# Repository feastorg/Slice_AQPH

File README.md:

# Slice Template

Template for creating BREAD slices.

## Introduction

[Short introduction on the project.]

## Usage

[Explain how to use the project. Include examples and screenshots if applicable.]

## pH front end

The pH electrode connects to the BNC (J2). U2 (CA3140) amplifies its EMF and
U4 (TL081H) inverts it about a 1.98 V offset taken from the -5 V rail. The
result reaches the Nano's A0 through R7 (4.7 kΩ); D2 (BAT54) clamps A0 to
ground if U4 swings negative.

| | |
| --- | --- |
| Span | pH 0-14 over 0-60 °C |
| U2 gain | 3.99 at RV1 mid-travel (the nominal setting) |
| Trim (RV1) | gain 3.81-4.19 (-4.6 % / +5.0 %) |
| A0 at nominal gain | 0.48-3.50 V at 0 °C, 0.34-3.64 V at 25 °C, 0.14-3.83 V at 60 °C (pH 0 is the low end) |
| Resolution | 48.3 counts/pH at 25 °C on the 10-bit 0-5 V ADC (44.2 at 0 °C, 54.0 at 60 °C) |
| Bandwidth | -3 dB at 0.53 Hz with a 100 MΩ electrode |

At maximum trim A0 reaches 0 V only past an EMF of 475 mV, beyond pH 0 at
60 °C (463 mV); pH 14 at 60 °C reads 3.92 V. These are nominal figures:
before calibration the op-amps' offsets and input current can move A0 by up
to about ±90 mV (about ±0.4 pH).

**Electrode.** Use a combination glass electrode of at most 500 MΩ near room
temperature. U2's input current (10 pA typical, 50 pA maximum at 25 °C in
the CA3140 data sheet) flows through the electrode's resistance: up to
25 mV of offset at 500 MΩ, and it grows with temperature, as does the
resistance of a cold electrode.
C5 (2.2 nF across U2's input) is a C0G part, KEMET C0805C222J5GACTU, with
an insulation resistance of at least 100 GΩ at 25 °C; with the electrode it
forms a divider that reads 0.1 % low on a 100 MΩ electrode and 1 % low on
1 GΩ, which the calibration takes out.
Calibrate with two buffers (pH 7 and pH 4 or 10) at the working temperature,
and correct the slope for temperature in firmware (0.198 mV/K per pH).

**No electrode.** With the BNC open, U2's input floats on C5 (2.2 nF) and its
input current walks it to one rail (about 5 mV/s at 10 pA, about 18 mV/s at
A0). A0 then sits either at about -0.2 V, held by D2 (the ADC reads 0), or
near the +5 V rail at U4's positive limit (close to full scale); which one
depends on the part. Treat readings below 0.1 V or above 4.9 V as no electrode or over-range.

The SPICE check in `hardware/sim/` (`python3 hardware/sim/check.py`)
checks the span, gain, trim cap, bandwidth and clamp figures against the
schematic.

## Documentation

Please refer to the [docs](/docs) for more info.

---

<div align="center">
  
</div>

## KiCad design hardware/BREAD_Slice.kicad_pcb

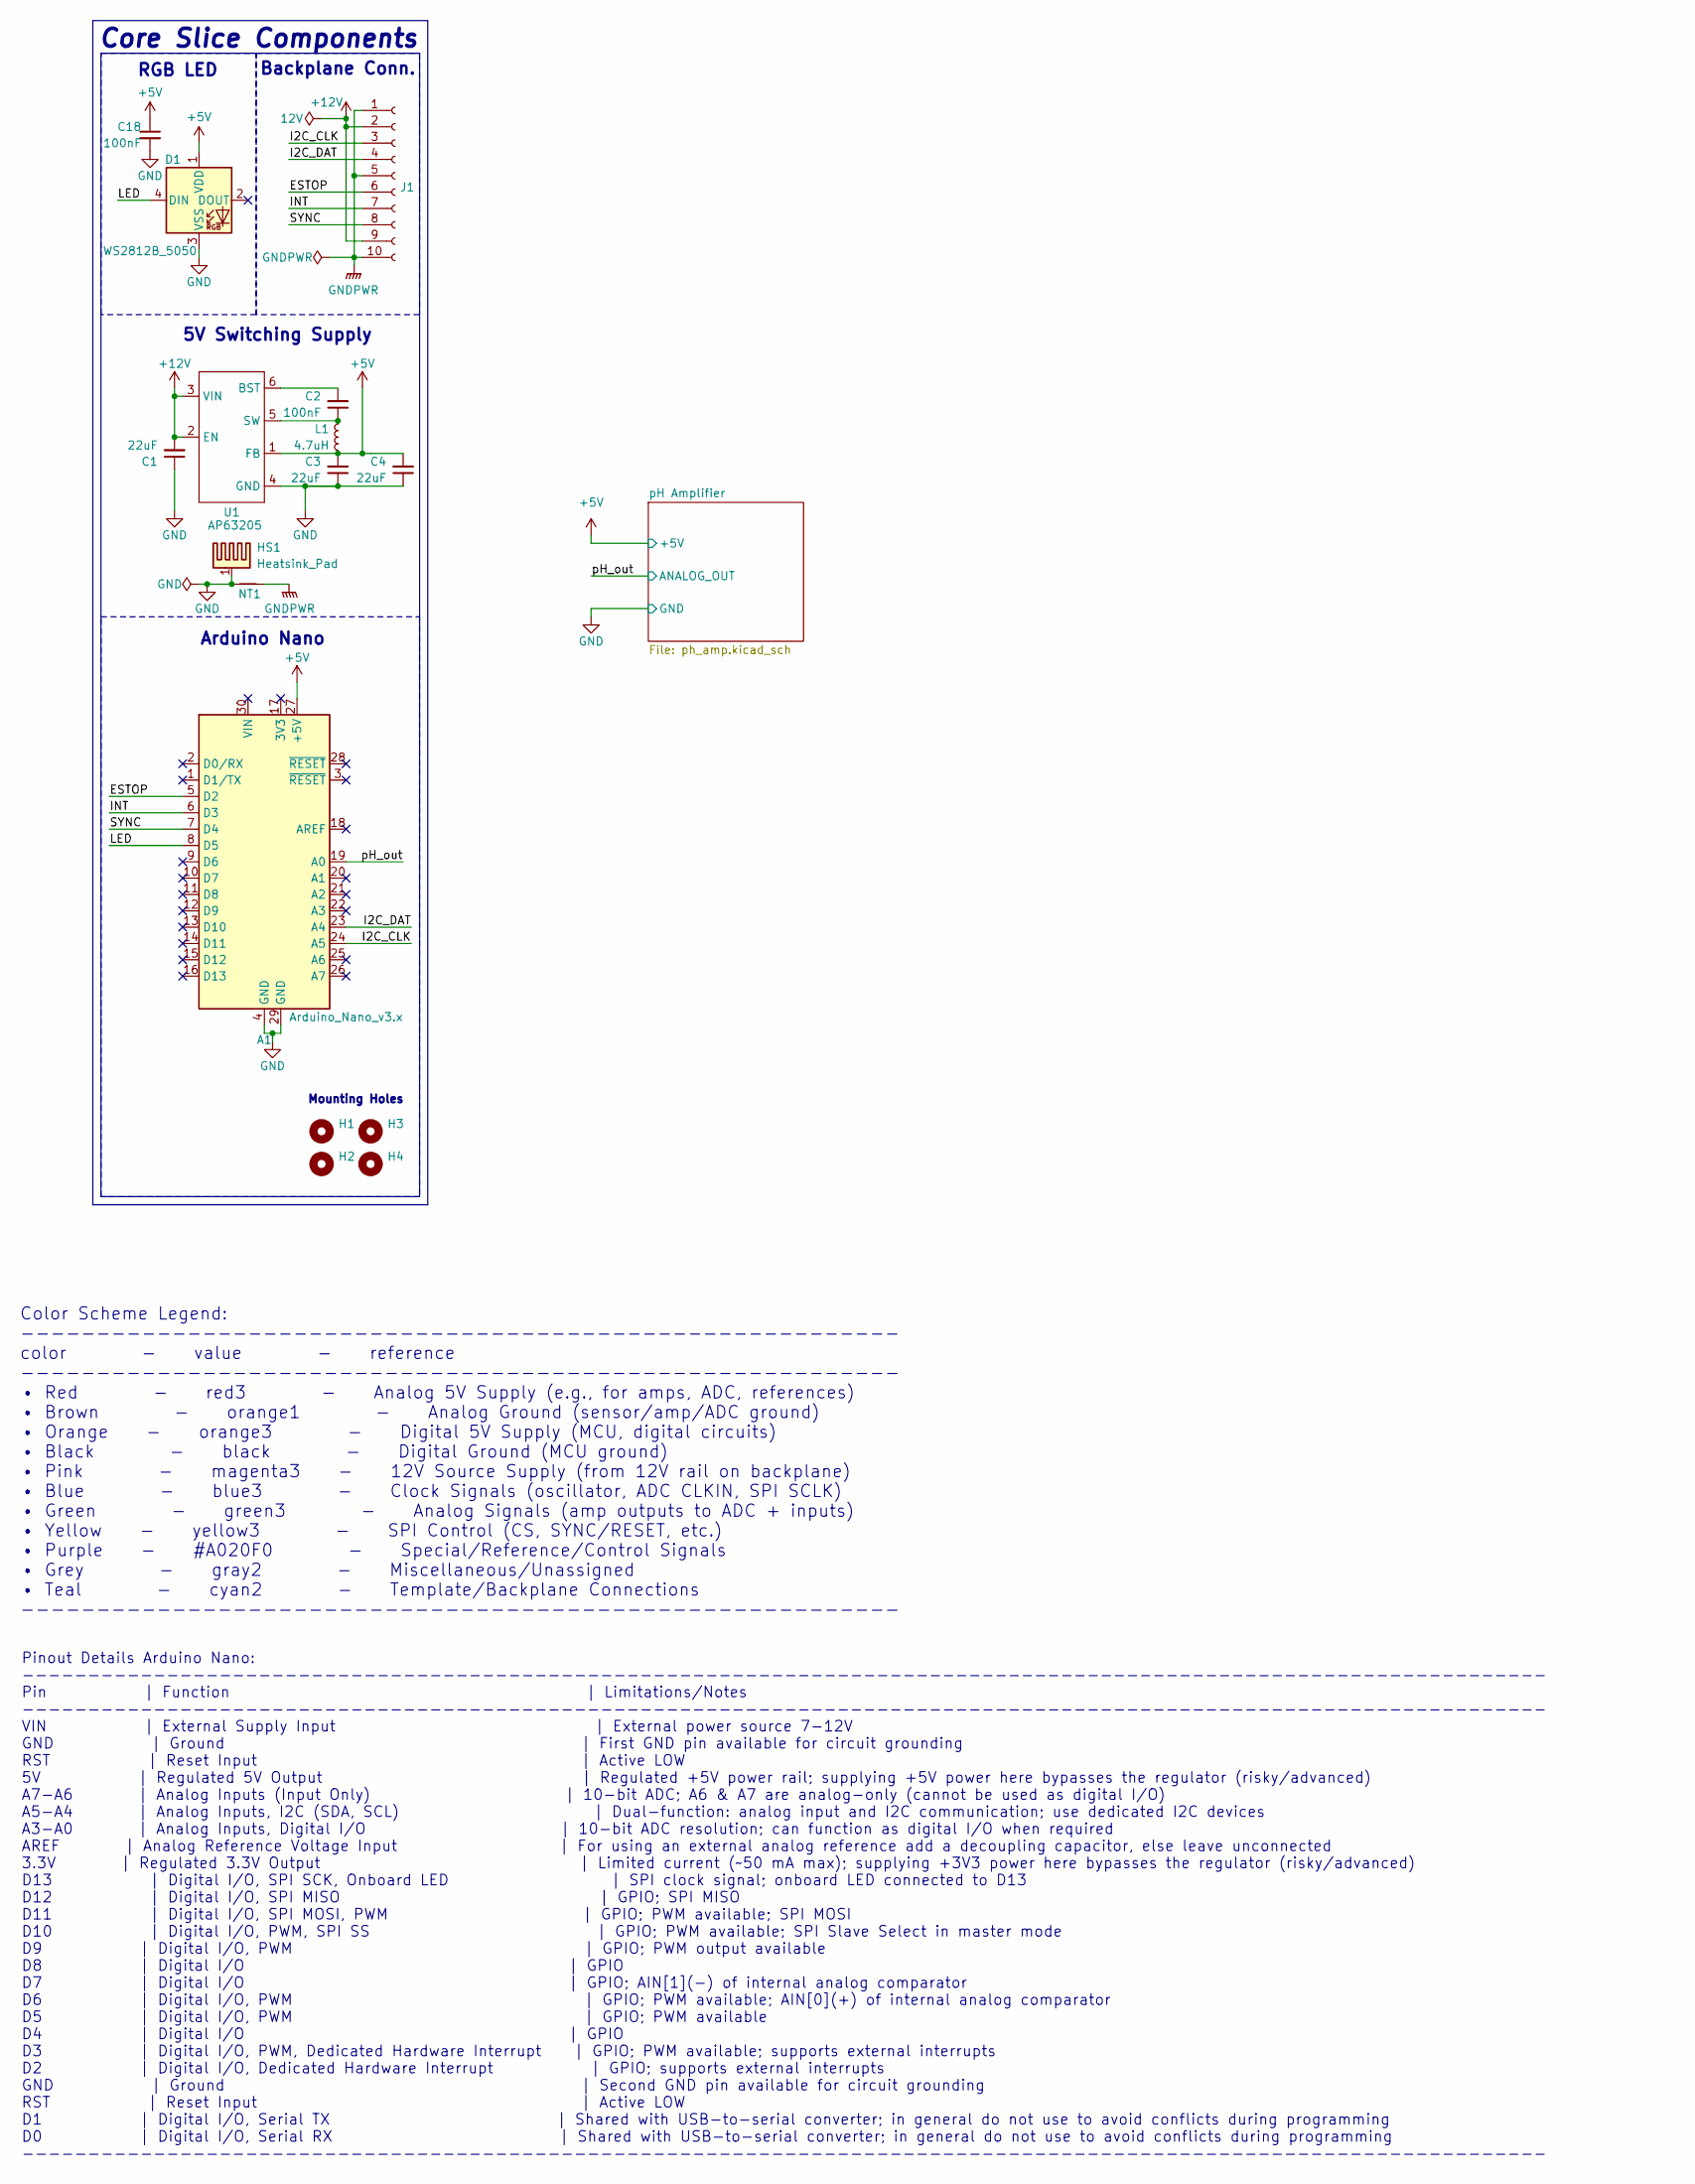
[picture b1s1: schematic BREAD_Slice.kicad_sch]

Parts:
A1: Arduino_Nano_v3.x; Arduino_Nano
C1, C3, C4: 22uF; C_1206_3216Metric
C2: 100nF; C_1206_3216Metric
C18: 100nF; C_0805_2012Metric_Pad1.18x1.45mm_HandSolder
D1: WS2812B_5050; WS2812-5050-4PIN
H1, H2, H3, H4: MountingHole; MountingHole_5mm
HS1: Heatsink_Pad; Thermal_Pad
J1: Conn_01x10_Female; PinSocket_1x10_P2.54mm_Horizontal
L1: 4.7uH; L_1210_3225Metric
NT1: NetTie_2; NetTie-2_SMD_Pad2.0mm
U1: AP63205; TSOT-23-6

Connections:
+5V: A1.27 (+5V), C3.2, C4.2, C18.1, D1.1 (VDD), L1.2, U1.1 (FB); also elsewhere on the board
+12V: C1.2, J1.2, J1.9, U1.2 (EN), U1.3 (VIN)
/ESTOP: A1.5 (D2), J1.6
/I2C_CLK: A1.24 (A5), J1.3
/I2C_DAT: A1.23 (A4), J1.4
/INT: A1.6 (D3), J1.7
/LED: A1.8 (D5), D1.4 (DIN)
/SYNC: A1.7 (D4), J1.8
/pH_out: A1.19 (A0); also elsewhere on the board
GND: A1.4 (GND), A1.29 (GND), C1.1, C3.1, C4.1, C18.2, D1.3 (VSS), HS1.1, NT1.1, U1.4 (GND); also elsewhere on the board
GNDPWR: J1.1, J1.5, J1.10, NT1.2
unnamed: C2.2, U1.6 (BST)
unnamed: C2.1, L1.1, U1.5 (SW)

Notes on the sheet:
5V Switching Supply
Pinout Details Arduino Nano: -------------------------------------------------------------------------------------------------------------------- Pin | Function | Limitations/Notes -------------------------------------------------------------------------------------------------------------------- V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
RGB LED
Color Scheme Legend: ---------------------------------------------------------- color - value - reference ---------------------------------------------------------- • Red - red3 - Analog 5V Supply (e.g., for amps, ADC, references) • Brown - orange1 - Analog Ground (sensor/amp/ADC ground) • Orange -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
Core Slice Components
Arduino Nano
Mounting Holes
Backplane Conn.

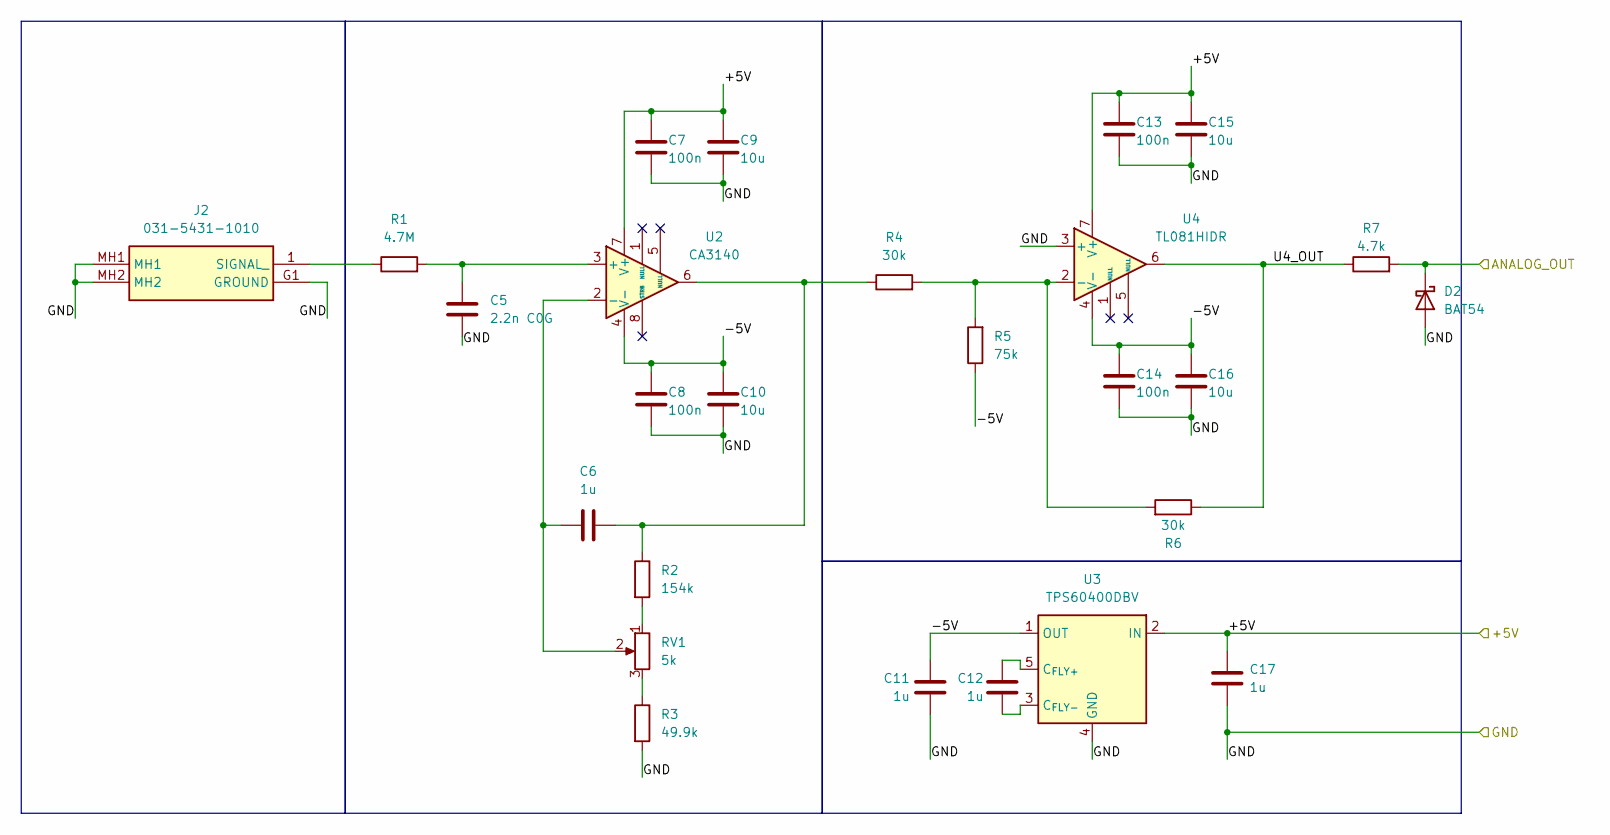
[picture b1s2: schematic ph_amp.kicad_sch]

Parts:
C5: 2.2n C0G; C_0805_2012Metric_Pad1.18x1.45mm_HandSolder; Manufacturer_Part_Number C0805C222J5GACTU
C6, C11, C12, C17: 1u; C_0805_2012Metric_Pad1.18x1.45mm_HandSolder
C7, C8, C13, C14: 100n; C_0805_2012Metric_Pad1.18x1.45mm_HandSolder
C9, C10, C15, C16: 10u; C_1206_3216Metric_Pad1.33x1.80mm_HandSolder
D2: BAT54; SOT-23
J2: 031-5431-1010; 03154311010; Mouser Part Number 523-31-5431-1010
R1: 4.7M; R_0805_2012Metric_Pad1.20x1.40mm_HandSolder
R2: 154k; R_0805_2012Metric_Pad1.20x1.40mm_HandSolder
R3: 49.9k; R_0805_2012Metric_Pad1.20x1.40mm_HandSolder
R4, R6: 30k; R_0805_2012Metric_Pad1.20x1.40mm_HandSolder
R5: 75k; R_0805_2012Metric_Pad1.20x1.40mm_HandSolder
R7: 4.7k; R_0805_2012Metric_Pad1.20x1.40mm_HandSolder
RV1: 5k; Potentiometer_Bourns_3296W_Vertical
U2: CA3140; SOIC-8_3.9x4.9mm_P1.27mm
U3: TPS60400DBV; SOT-23-5
U4: TL081HIDR; SOIC-8_3.9x4.9mm_P1.27mm

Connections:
+5V: C7.1, C9.1, C13.1, C15.1, C17.1, U2.7 (V+), U3.2 (IN), U4.7 (V+); also elsewhere on the board
/pH Amplifier/-5V: C8.1, C10.1, C11.1, C14.1, C16.1, R5.1, U2.4 (V-), U3.1 (OUT), U4.4 (V-)
/pH Amplifier/U4_OUT: R6.1, R7.1, U4.6
/pH_out: D2.3 (K), R7.2; also elsewhere on the board
GND: C5.2, C7.2, C8.2, C9.2, C10.2, C11.2, C13.2, C14.2, C15.2, C16.2, C17.2, D2.1 (A), J2.G1 (GROUND), J2.MH1, J2.MH2, R3.2, U3.4 (GND), U4.3 (+); also elsewhere on the board
unnamed: C6.2, R2.1, R4.1, U2.6
unnamed: J2.1 (SIGNAL_), R1.1
unnamed: R2.2, RV1.1
unnamed: R3.1, RV1.3
unnamed: C5.1, R1.2, U2.3 (+)
unnamed: C6.1, RV1.2, U2.2 (-)
unnamed: C12.1, U3.5 (C_{FLY+})
unnamed: C12.2, U3.3 (C_{FLY-})
unnamed: R4.2, R5.2, R6.2, U4.2 (-)

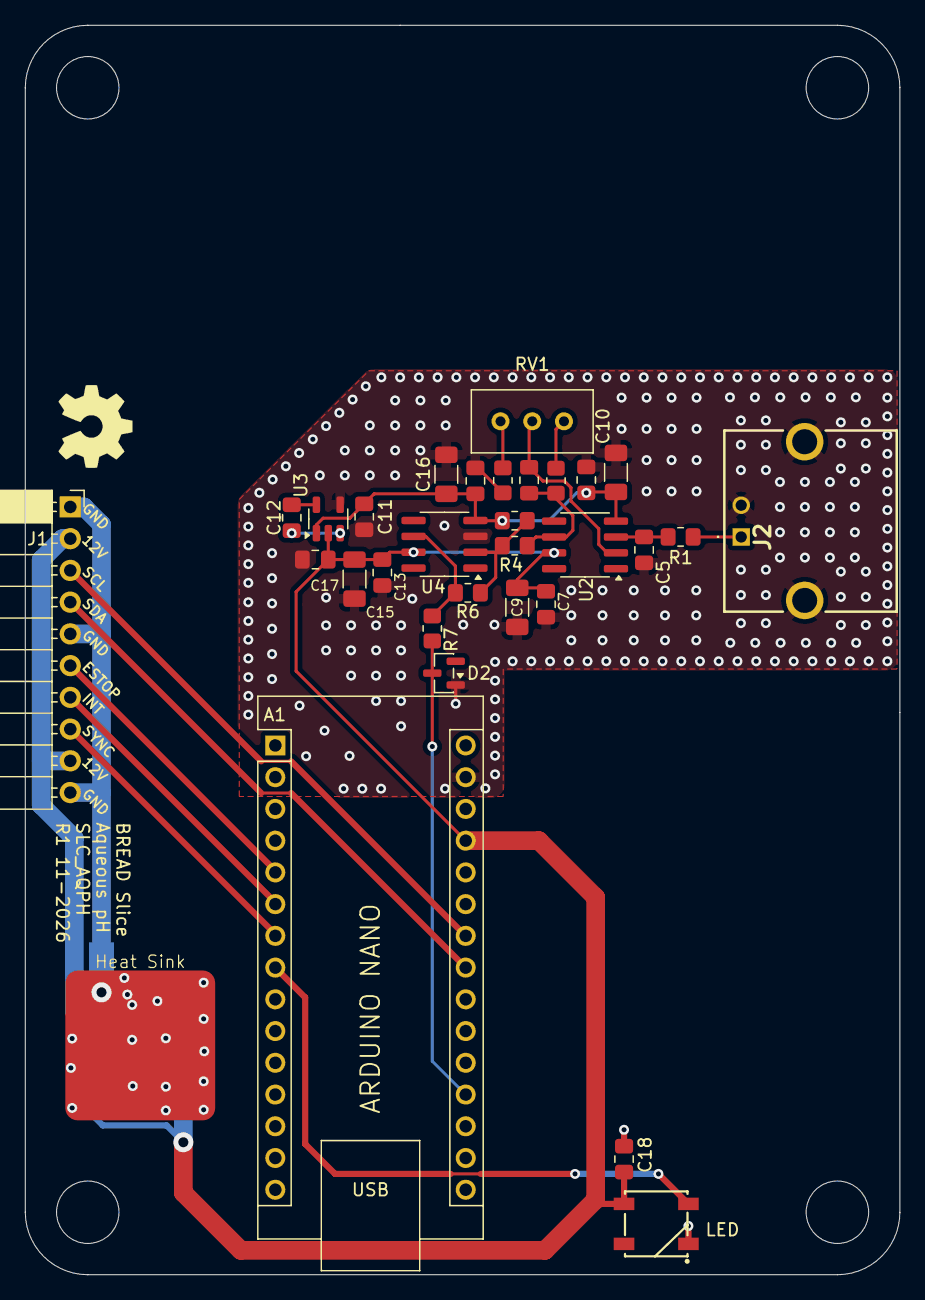
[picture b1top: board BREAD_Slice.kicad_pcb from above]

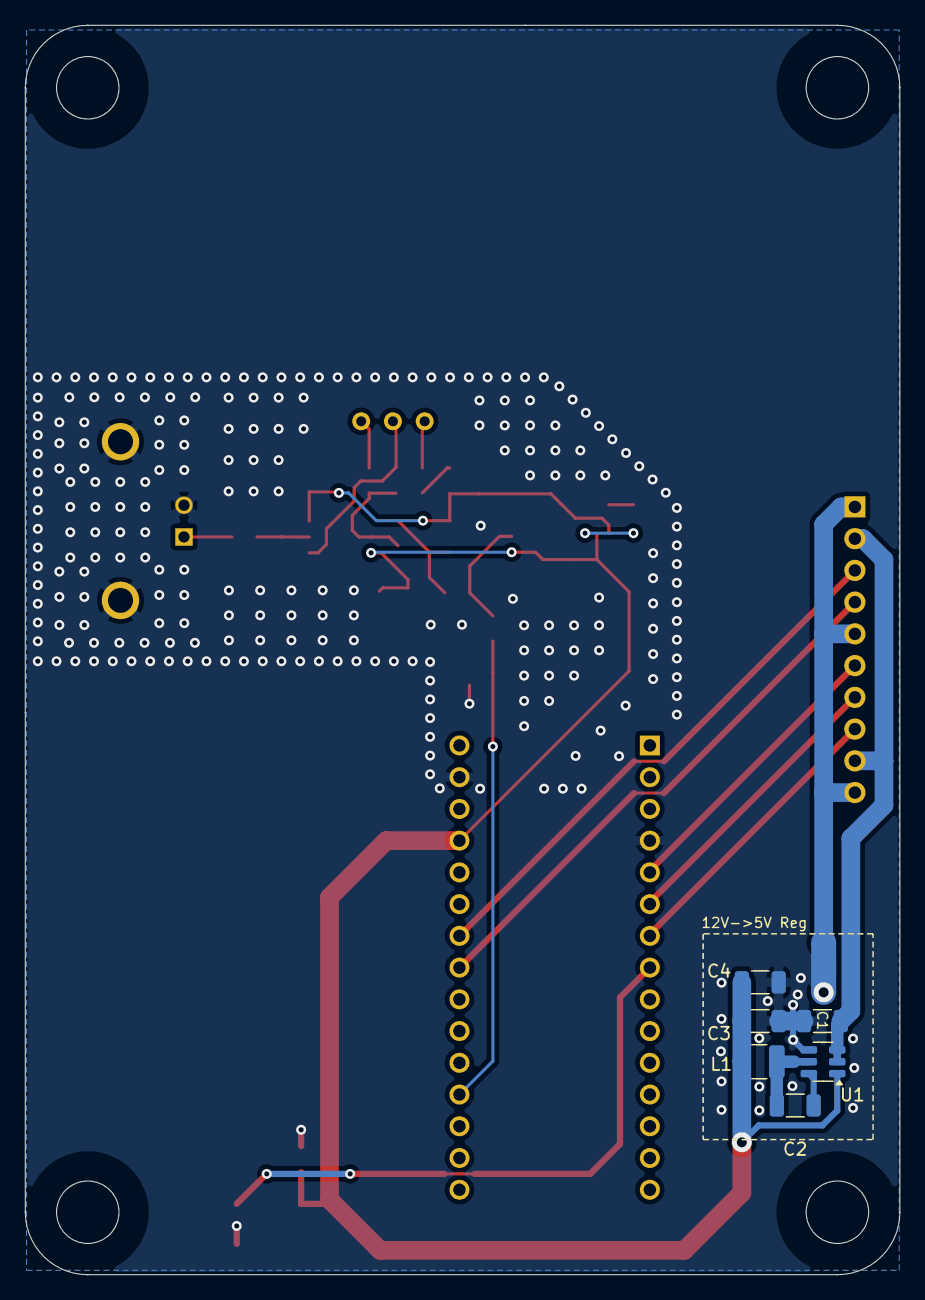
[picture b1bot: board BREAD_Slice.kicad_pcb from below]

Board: 2 copper layers, 70.0 x 100.0 mm, 43 parts (7 on the bottom side), 24 nets.

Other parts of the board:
Logo1: Logo_Open_Hardware_Small; OSHW-Symbol_6.7x6mm_SilkScreen

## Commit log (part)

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2025-04-17 updated docs
2025-04-17 added reference
2026-04-18 chore: minor update
2026-05-20 Add slice.yaml manifest (schema v1.0)
2026-05-24 Add KiBot/docs pipeline
2026-05-24 Update TODO with CI findings (DRC errors)
